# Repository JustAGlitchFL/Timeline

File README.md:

# Timeline
Video/photo editing keyboard tuned for Davinci Resolve

## Why
I edit in Blackmagic Design DaVinci Resolve, and would like to have something a little smoother than a keyboard and mouse. BD sells the Speed Editor, but it costs US$435, which is kinda insane. 

I felt I might as well make my own version of this, so I created this as a largely 1:1 clone of the layout with a custom design

## Assembly/Other info
This does not include a case, as I wanted to keep it low to the table, and to keep the bare PCB aesthetic I enjoy. Solder the parts as they fit into the board, then apply some 3M 2229 to the bottom of the board to resuce sliding, and to protect the board/desk.  

## BOM
|q  |part             |link                                                     |price       |total |
|---|-----------------|---------------------------------------------------------|------------|------|
|1  |pcb              |                                                         |$45.70      |$72.86|
|55 |switches         |                                                         |have on hand|      |
|2  |ECE11 with clicks|https://www.mouser.com/ProductDetail/688-EC11E15204A3    |$7.36       |      |
|1  |Smooth EC11      |https://www.mouser.com/ProductDetail/688-EC11E1834403    |$4.68       |      |
|   |Vibration Motor  |https://www.mouser.com/ProductDetail/665-HD-EM0802-LW30-R|$3.93       |      |
|   |mouser shipping  |                                                         |$7.99       |      |
|   |mouser DDP       |                                                         |$3.20       |      |

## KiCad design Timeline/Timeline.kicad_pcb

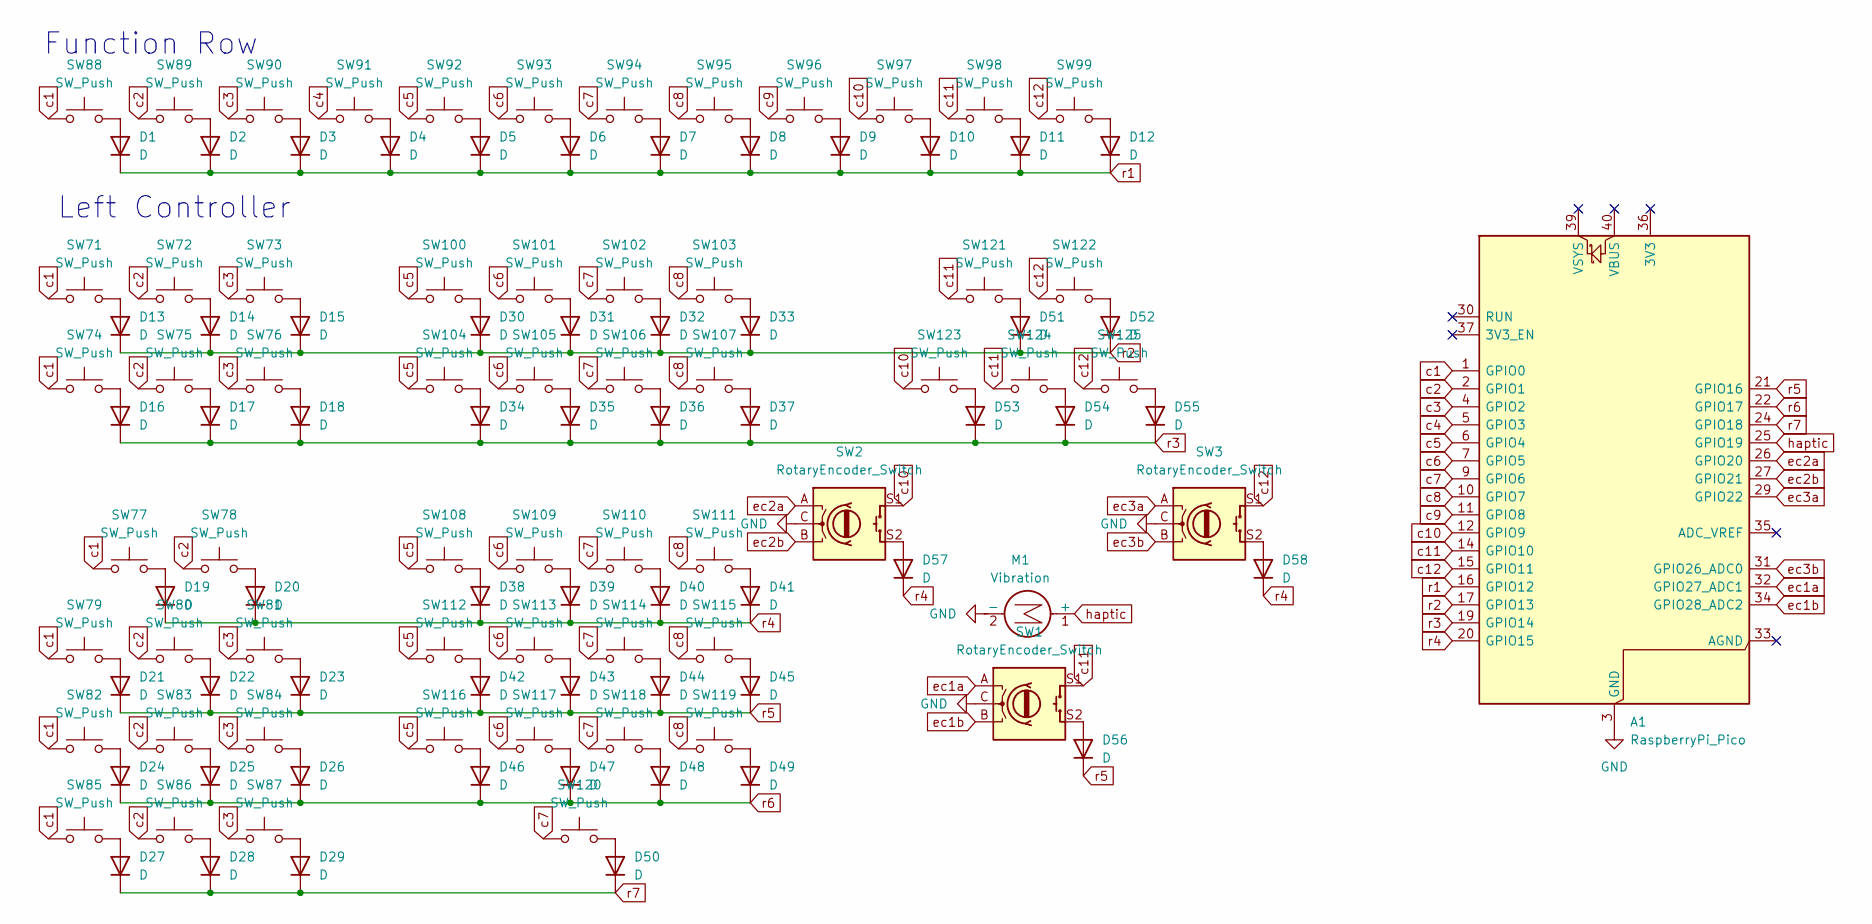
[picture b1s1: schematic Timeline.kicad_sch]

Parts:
A1: RaspberryPi_Pico; RaspberryPi_Pico_Common_SMD noantenna
D1, D2, D3, D4, D5, D6, D7, D8, D9, D10, D11, D12, D13, D14, D15, D16, D17, D18, D19, D20, D21, D22, D23, D24, D25, D26, D27, D28, D29, D30, D31, D32, D33, D34, D35, D36, D37, D38, D39, D40, D41, D42, D43, D44, D45, D46, D47, D48, D49, D50, D51, D52, D53, D54, D55, D56, D57, D58: D; D_0805_2012Metric_Pad1.15x1.40mm_HandSolder
M1: Vibration; PinHeader_1x02_P1.00mm_Vertical
SW1, SW2, SW3: RotaryEncoder_Switch; RotaryEncoder_Alps_EC11E-Switch_Vertical_H20mm
SW71, SW72, SW73, SW74, SW75, SW76, SW79, SW80, SW81, SW82, SW83, SW84, SW85, SW86, SW87, SW88, SW89, SW90, SW91, SW92, SW93, SW94, SW95, SW96, SW97, SW98, SW99, SW100, SW101, SW102, SW103, SW104, SW105, SW106, SW107, SW108, SW109, SW110, SW111, SW112, SW113, SW114, SW115, SW116, SW117, SW118, SW119, SW123, SW124, SW125: SW_Push; Hotswap_MX_1.00u
SW77, SW78, SW121, SW122: SW_Push; Hotswap_MX_1.50u
SW120: SW_Push; Hotswap_MX_2.00u

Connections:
GND: A1.3 (GND), A1.8 (GND), A1.13 (GND), A1.18 (GND), A1.23 (GND), A1.28 (GND), A1.38 (GND), M1.2 (-), SW1.C, SW2.C, SW3.C
unnamed: D1.2 (A), SW88.2
unnamed: D2.2 (A), SW89.2
unnamed: D3.2 (A), SW90.2
unnamed: D4.2 (A), SW91.2
unnamed: D5.2 (A), SW92.2
unnamed: D6.2 (A), SW93.2
unnamed: D7.2 (A), SW94.2
unnamed: D8.2 (A), SW95.2
unnamed: D9.2 (A), SW96.2
unnamed: D10.2 (A), SW97.2
unnamed: D11.2 (A), SW98.2
unnamed: D12.2 (A), SW99.2
unnamed: D13.2 (A), SW71.2
unnamed: D14.2 (A), SW72.2
unnamed: D15.2 (A), SW73.2
unnamed: D16.2 (A), SW74.2
unnamed: D17.2 (A), SW75.2
unnamed: D18.2 (A), SW76.2
unnamed: D19.2 (A), SW77.2
unnamed: D20.2 (A), SW78.2
unnamed: D21.2 (A), SW79.2
unnamed: D22.2 (A), SW80.2
unnamed: D23.2 (A), SW81.2
unnamed: D24.2 (A), SW82.2
unnamed: D25.2 (A), SW83.2
unnamed: D26.2 (A), SW84.2
unnamed: D27.2 (A), SW85.2
unnamed: D28.2 (A), SW86.2
unnamed: D29.2 (A), SW87.2
unnamed: D30.2 (A), SW100.2
unnamed: D31.2 (A), SW101.2
unnamed: D32.2 (A), SW102.2
unnamed: D33.2 (A), SW103.2
unnamed: D34.2 (A), SW104.2
unnamed: D35.2 (A), SW105.2
unnamed: D36.2 (A), SW106.2
unnamed: D37.2 (A), SW107.2
unnamed: D38.2 (A), SW108.2
unnamed: D39.2 (A), SW109.2
unnamed: D40.2 (A), SW110.2
unnamed: D41.2 (A), SW111.2
unnamed: D42.2 (A), SW112.2
unnamed: D43.2 (A), SW113.2
unnamed: D44.2 (A), SW114.2
unnamed: D45.2 (A), SW115.2
unnamed: D46.2 (A), SW116.2
unnamed: D47.2 (A), SW117.2
unnamed: D48.2 (A), SW118.2
unnamed: D49.2 (A), SW119.2
unnamed: D50.2 (A), SW120.2
unnamed: D51.2 (A), SW121.2
unnamed: D52.2 (A), SW122.2
unnamed: D53.2 (A), SW123.2
unnamed: D54.2 (A), SW124.2
unnamed: D55.2 (A), SW125.2
unnamed: D56.2 (A), SW1.S2
unnamed: D57.2 (A), SW2.S2
unnamed: D58.2 (A), SW3.S2
c1: A1.1 (GPIO0), SW71.1, SW74.1, SW77.1, SW79.1, SW82.1, SW85.1, SW88.1
c2: A1.2 (GPIO1), SW72.1, SW75.1, SW78.1, SW80.1, SW83.1, SW86.1, SW89.1
c3: A1.4 (GPIO2), SW73.1, SW76.1, SW81.1, SW84.1, SW87.1, SW90.1
c4: A1.5 (GPIO3), SW91.1
c5: A1.6 (GPIO4), SW92.1, SW100.1, SW104.1, SW108.1, SW112.1, SW116.1
c6: A1.7 (GPIO5), SW93.1, SW101.1, SW105.1, SW109.1, SW113.1, SW117.1
c7: A1.9 (GPIO6), SW94.1, SW102.1, SW106.1, SW110.1, SW114.1, SW118.1, SW120.1
c8: A1.10 (GPIO7), SW95.1, SW103.1, SW107.1, SW111.1, SW115.1, SW119.1
c9: A1.11 (GPIO8), SW96.1
c10: A1.12 (GPIO9), SW2.S1, SW97.1, SW123.1
c11: A1.14 (GPIO10), SW1.S1, SW98.1, SW121.1, SW124.1
c12: A1.15 (GPIO11), SW3.S1, SW99.1, SW122.1, SW125.1
ec1a: A1.32 (GPIO27_ADC1), SW1.A
ec1b: A1.34 (GPIO28_ADC2), SW1.B
ec2a: A1.26 (GPIO20), SW2.A
ec2b: A1.27 (GPIO21), SW2.B
ec3a: A1.29 (GPIO22), SW3.A
ec3b: A1.31 (GPIO26_ADC0), SW3.B
haptic: A1.25 (GPIO19), M1.1 (+)
r1: A1.16 (GPIO12), D1.1 (K), D2.1 (K), D3.1 (K), D4.1 (K), D5.1 (K), D6.1 (K), D7.1 (K), D8.1 (K), D9.1 (K), D10.1 (K), D11.1 (K), D12.1 (K)
r2: A1.17 (GPIO13), D13.1 (K), D14.1 (K), D15.1 (K), D30.1 (K), D31.1 (K), D32.1 (K), D33.1 (K), D51.1 (K), D52.1 (K)
r3: A1.19 (GPIO14), D16.1 (K), D17.1 (K), D18.1 (K), D34.1 (K), D35.1 (K), D36.1 (K), D37.1 (K), D53.1 (K), D54.1 (K), D55.1 (K)
r4: A1.20 (GPIO15), D19.1 (K), D20.1 (K), D38.1 (K), D39.1 (K), D40.1 (K), D41.1 (K), D57.1 (K), D58.1 (K)
r5: A1.21 (GPIO16), D21.1 (K), D22.1 (K), D23.1 (K), D42.1 (K), D43.1 (K), D44.1 (K), D45.1 (K), D56.1 (K)
r6: A1.22 (GPIO17), D24.1 (K), D25.1 (K), D26.1 (K), D46.1 (K), D47.1 (K), D48.1 (K), D49.1 (K)
r7: A1.24 (GPIO18), D27.1 (K), D28.1 (K), D29.1 (K), D50.1 (K)

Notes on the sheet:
Left Controller
Function Row

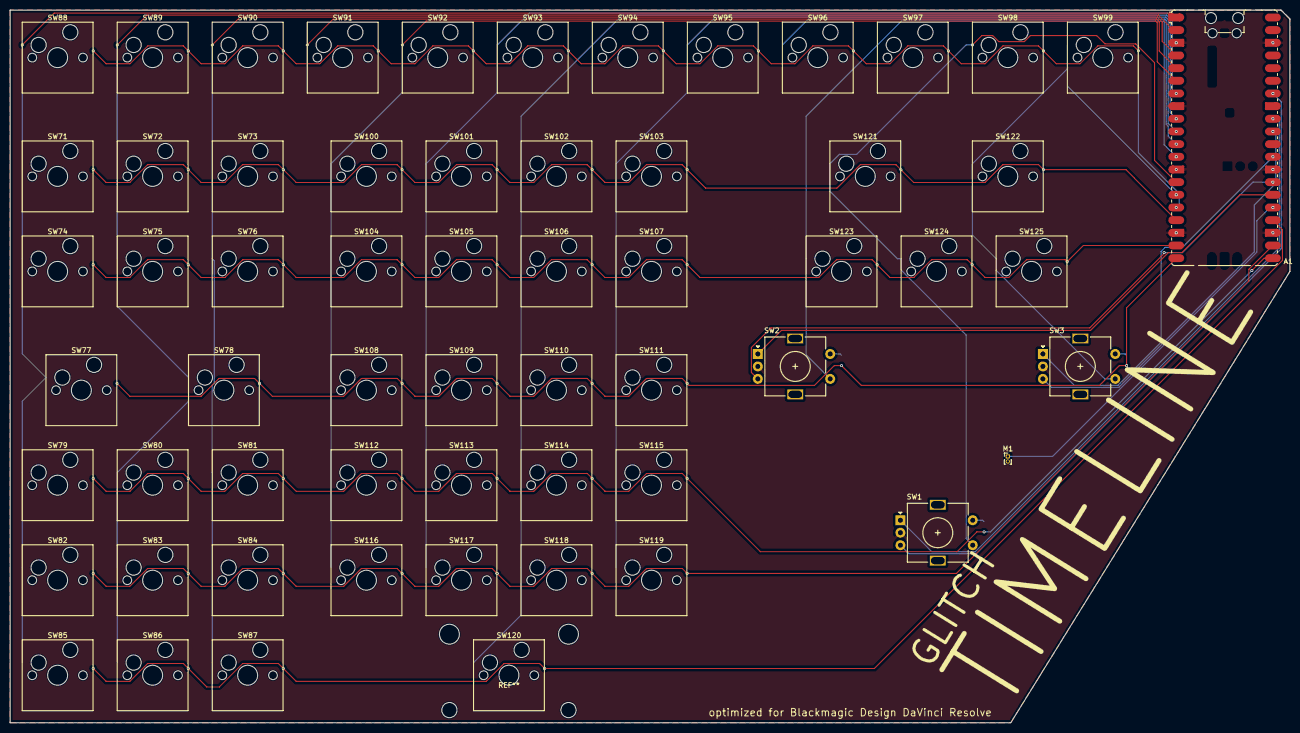
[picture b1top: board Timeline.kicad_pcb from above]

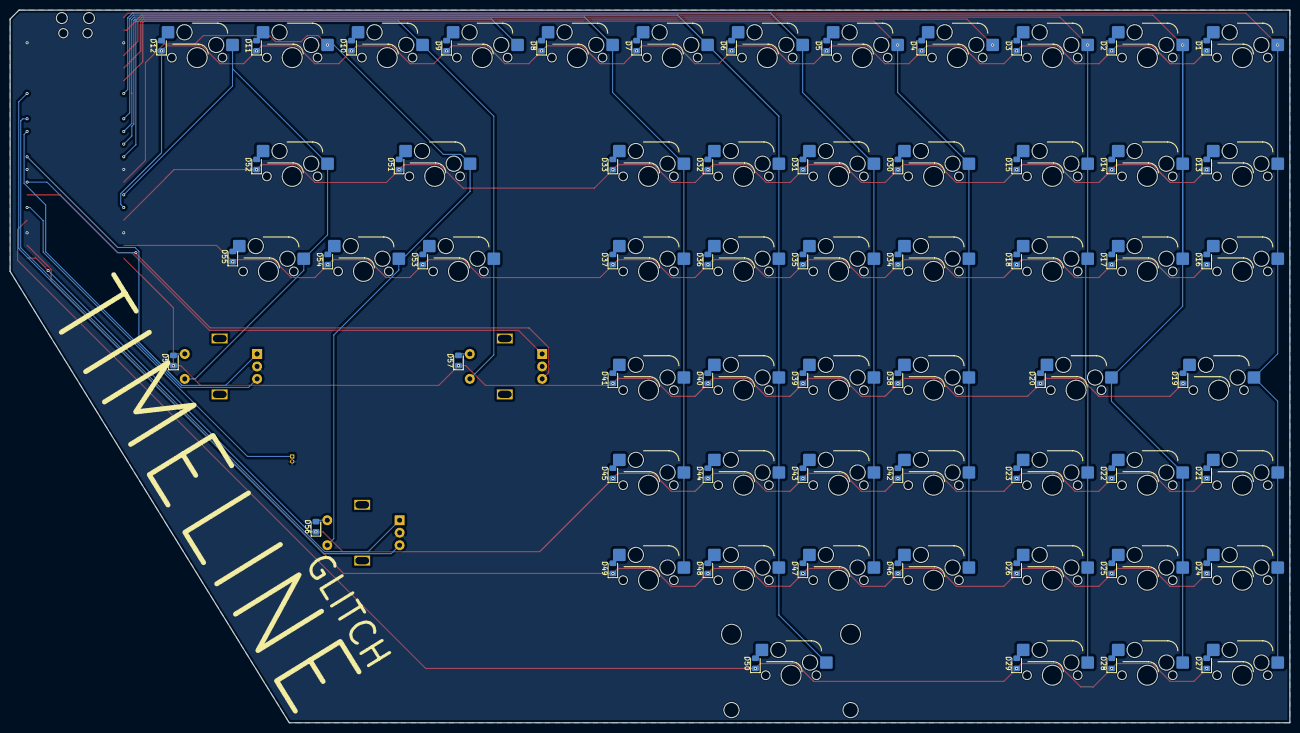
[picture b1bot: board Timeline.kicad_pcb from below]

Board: 2 copper layers, 256.6 x 142.9 mm, 118 parts (58 on the bottom side), 85 nets.

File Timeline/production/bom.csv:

Designator,Footprint,Quantity,Value,LCSC Part #
A1,RaspberryPi_Pico_Common_SMD noantenna,1,RaspberryPi_Pico,
"D1, D10, D11, D12, D13, D14, D15, D16, D17, D18, D19, D2, D20, D21, D22, D23, D24, D25, D26, D27, D28, D29, D3, D30, D31, D32, D33, D34, D35, D36, D37, D38, D39, D4, D40, D41, D42, D43, D44, D45, D46, D47, D48, D49, D5, D50, D51, D52, D53, D54, D55, D56, D57, D58, D6, D7, D8, D9",0805,58,D,
M1,PinHeader_1x02_P1.00mm_Vertical,1,Vibration,
"SW1, SW2, SW3",RotaryEncoder_Alps_EC11E-Switch_Vertical_H20mm,3,RotaryEncoder_Switch,
"SW100, SW101, SW102, SW103, SW104, SW105, SW106, SW107, SW108, SW109, SW110, SW111, SW112, SW113, SW114, SW115, SW116, SW117, SW118, SW119, SW123, SW124, SW125, SW71, SW72, SW73, SW74, SW75, SW76, SW79, SW80, SW81, SW82, SW83, SW84, SW85, SW86, SW87, SW88, SW89, SW90, SW91, SW92, SW93, SW94, SW95, SW96, SW97, SW98, SW99",Hotswap_MX_1.00u,50,SW_Push,
SW120,Hotswap_MX_2.00u,1,SW_Push,
"SW121, SW122, SW77, SW78",Hotswap_MX_1.50u,4,SW_Push,

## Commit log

2025-07-23 schematic
2025-07-31 sync
2025-07-31 images
2025-08-01 sync bom
